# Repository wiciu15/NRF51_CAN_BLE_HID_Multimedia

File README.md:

#### *TLDR: Controlling spotify on the phone, with car's CAN bus*

This project is a ***work in progress***. Comes with no warranty. Vehicles CAN-bus is a powerful tool, ***use at your own risk***, author does not have responsibility for any damage on property or health.

Intended for ***2011-2013 Chevrolet Volt***, may work with other General Motors Global Platform A cars.
Uses own ***MCP2515 CAN controller*** chip library to interact with CAN-bus (Low-speed SWCAN/GMLAN in General Motors Vehicles).

Nordic ***NRF51822 microcontroler*** is in charge of Bluetooth LE connection and HID protocol.
HID report descriptor is custom and supports only 7 consumer control(multimedia) keys, like Play/Pause, Scan Next, Scan Prev, Mute.

CAN frames processing is offloaded to MCP2515 with usage of filters, to reduce uC usage and energy efficiency.
While MCP2515 is used in normal operating mode, device should not transmit anything other than error/ack frames.

PCB design needs some fixes and further testing. As of this moment 16Mhz crystal footprint is mirrored, MCP2515 INT pin needs a pullup resistor and SWDIO/RST pullup+optional power-on-reset 2.2u capacitor.

**[Project log on hackaday.io](https://hackaday.io/project/176834-chevy-volt-sw-can-ble-multimedia-control)**

Provided files are Eclipse GNU MCU Embedded project. To build it you need to also provide NRF SDK v12.3 (include directories), GCC arm-none-eabi compiler, and OpenOCD to use flash script (flash.bat file) with ST-Link v2 SWD programmer.

Software contains code from linux kernel CAN driver, and open-usb-can project by Fabio Baltieri.

**Software licensed under GNU General Public License v3.**
This program is free software: you can redistribute it and/or modify
it under the terms of the GNU General Public License as published by
the Free Software Foundation, either version 3 of the License, or
(at your option) any later version.

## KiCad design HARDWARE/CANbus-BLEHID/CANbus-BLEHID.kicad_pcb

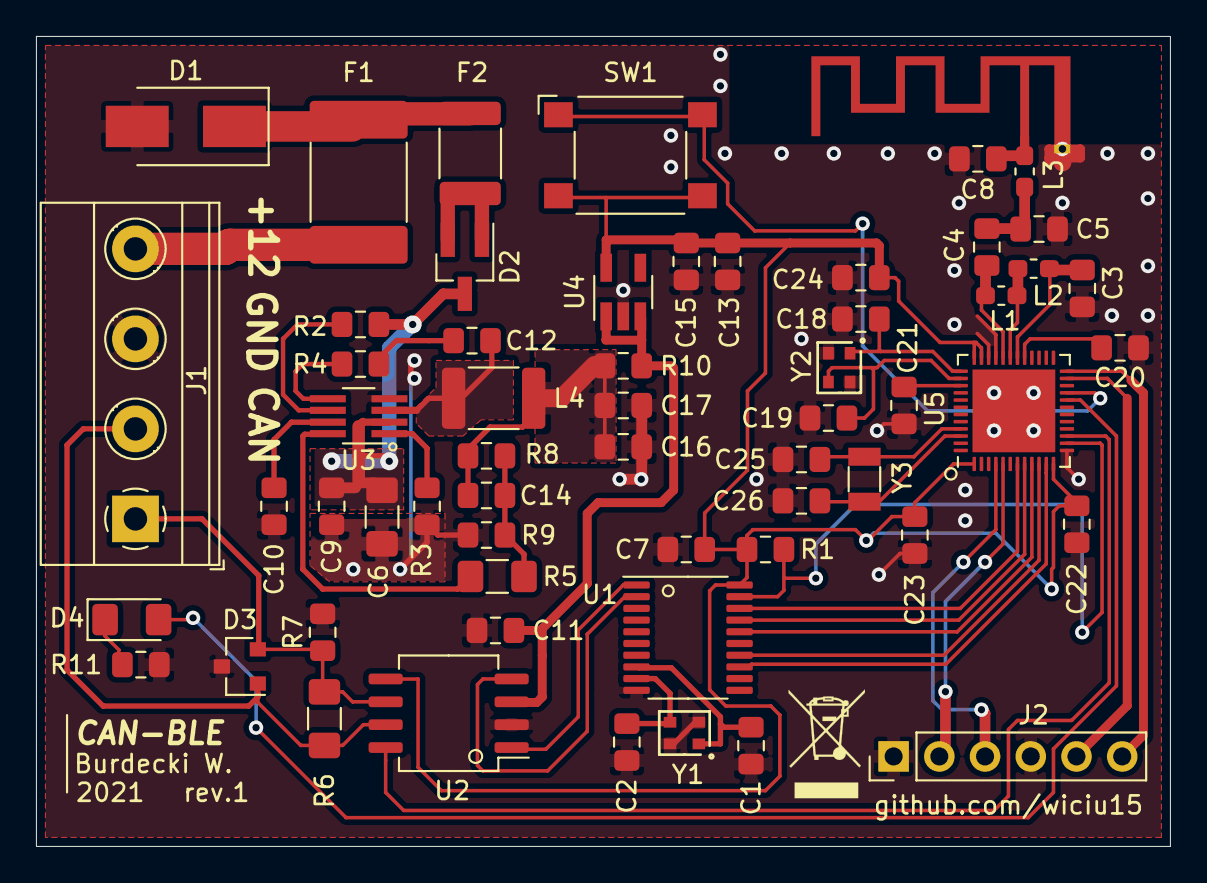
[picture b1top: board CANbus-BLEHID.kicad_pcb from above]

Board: 2 copper layers, 63.0 x 45.0 mm, 59 parts (0 on the bottom side), 47 nets.

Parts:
AE1: 2.45 GHz PCB antenna; Texas_SWRA117D_2.4GHz_Left
C1, C2, C14, C18, C19, C25, C26: 12pF; C_0805_2012Metric_Pad1.15x1.40mm_HandSolder
C3: 2.2n; C_0805_2012Metric_Pad1.15x1.40mm_HandSolder
C4: 3.9p; C_0805_2012Metric_Pad1.15x1.40mm_HandSolder
C5: 1p; C_0805_2012Metric_Pad1.15x1.40mm_HandSolder
C6: 10u 16V; C_1206_3216Metric_Pad1.42x1.75mm_HandSolder
C7, C9, C10, C11, C12, C15, C17, C20, C21, C22, C23: 100n; C_0805_2012Metric_Pad1.15x1.40mm_HandSolder
C8: 1.5p; C_0805_2012Metric_Pad1.15x1.40mm_HandSolder
C13, C16: 22u 6,3V; C_0805_2012Metric_Pad1.15x1.40mm_HandSolder
C24: 1n; C_0805_2012Metric_Pad1.15x1.40mm_HandSolder
D1: SM6T15CA; D_SMB_Handsoldering
D2: BAV70; SOT-23_Handsoldering
D3: PESD1CAN; SOT-23
D4: LED; LED_1206_3216Metric_Pad1.42x1.75mm_HandSolder
F1: 0ZCF0200AF2C; Fuse_2920_7451Metric_Pad2.10x5.45mm_HandSolder
F2: 0ZCK0010FF2G; Fuse_1812_4532Metric_Pad1.30x3.40mm_HandSolder
J1: AC300V-04P-5.0; TerminalBlock_Phoenix_MKDS-1,5-4_1x04_P5.00mm_Horizontal
J2: UART; PinHeader_1x06_P2.54mm_Vertical
L1: 4.7n; L_0603_1608Metric_Pad1.05x0.95mm_HandSolder
L2: 27n; L_0603_1608Metric_Pad1.05x0.95mm_HandSolder
L3: 3.3n; L_0603_1608Metric_Pad1.05x0.95mm_HandSolder
L4: NL12KTC5R6; L_1812_4532Metric_Pad1.30x3.40mm_HandSolder
R1: 10k; R_0805_2012Metric_Pad1.15x1.40mm_HandSolder
R2, R3: 75k; R_0805_2012Metric_Pad1.15x1.40mm_HandSolder
R4: 20R; R_0805_2012Metric_Pad1.15x1.40mm_HandSolder
R5: 20k; R_1206_3216Metric_Pad1.42x1.75mm_HandSolder
R6: 120R; R_1206_3216Metric_Pad1.42x1.75mm_HandSolder
R7, R10: 0R; R_0805_2012Metric_Pad1.15x1.40mm_HandSolder
R8: 40,2k; R_0805_2012Metric_Pad1.15x1.40mm_HandSolder
R9: 7,5k; R_0805_2012Metric_Pad1.15x1.40mm_HandSolder
R11: 1k; R_0805_2012Metric_Pad1.15x1.40mm_HandSolder
SW1: SW_Push_Dual; SW_SPST_Omron_B3FS-100xP
U1: MCP2515-xST; TSSOP-20_4.4x6.5mm_P0.65mm
U2: TLE7250V; SO-8_5.3x6.2mm_P1.27mm
U3: MP2315GJ-Z; TSOT-23-8_HandSoldering
U4: MIC5504-3.3YM5; SOT-23-5_HandSoldering
U5: nRF51822-QFAC; QFN-48-1EP_6x6mm_P0.4mm_EP4.6x4.6mm
Y1, Y2: 16M; XT224-16
Y3: 32,768k; Crystal_SMD_3215-2Pin_3.2x1.5mm

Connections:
+3V3: C7.2, C13.1, C15.2, C22.2, C23.2, C24.2, R1.1, SW1.3, SW1.4, U1.20, U2.5, U4.5, U5.1, U5.12, U5.35, U5.36
+5V: C11.2, R10.1, U2.3, U4.1, U4.3
ANT1: L1.2, L2.1, U5.31
ANT2: C4.2, L1.1, U5.32
CANH: D3.1, J1.2, R6.1, U2.7
CANL: D3.2, J1.1, R6.2, R7.1, U2.6
GND: AE1.2, C1.2, C2.2, C3.1, C5.1, C6.2, C7.1, C8.1, C9.1, C10.1, C11.1, C13.2, C15.1, C16.2, C17.1, C18.2, C19.2, C20.1, C21.1, C22.1, C23.1, C24.1, C25.1, C26.1, D1.2, D3.3, J1.3, J2.1, J2.4, R3.2, R7.2, R9.2, R11.1, U1.10, U2.2, U3.4, U4.2, U5.13, U5.33, U5.34, U5.49
MCP2515_INT: U1.13, U5.11
MCP2515_RST: R1.2, U1.19, U5.14
unnamed: AE1.1, C8.2, L3.2
unnamed: C1.1, U1.8, Y1.1
unnamed: C2.1, U1.9, Y1.2
unnamed: C4.1, C5.2, L3.1
unnamed: C6.1, C9.2, D2.3, R2.1, U3.2
unnamed: C10.2, U3.7
unnamed: C12.1, R4.1
unnamed: C12.2, L4.1, U3.3
unnamed: C14.1, R5.2, R8.2, R9.1
unnamed: C14.2, C16.1, C17.2, L4.2, R8.1, R10.2
unnamed: C18.1, U5.37, Y2.1
unnamed: C19.1, U5.38, Y2.2
unnamed: C20.2, U5.29
unnamed: C21.2, U5.39
unnamed: C25.2, U5.45, Y3.1
unnamed: C26.2, U5.46, Y3.2
unnamed: D1.1, F1.1, F2.2
unnamed: D2.1, D2.2, F2.1
unnamed: D4.1, R11.2
unnamed: D4.2, U5.20
unnamed: F1.2, J1.4
unnamed: R2.2, U3.6
unnamed: R3.1, U3.1
unnamed: R4.2, U3.5
unnamed: R5.1, U3.8
unnamed: SW1.1, SW1.2, U5.21
unnamed: U1.1, U2.1
unnamed: U1.2, U2.4
SPI_CS: U1.18, U5.7
SPI_MISO: U1.17, U5.8
SPI_MOSI: U1.16, U5.9
SPI_SCK: U1.14, U5.10
SWCLK: J2.6, U5.24
SWDIO: J2.5, U5.23
TLE7250_NEN: U2.8, U5.15
UART_RX: J2.2, U5.5
UART_TX: J2.3, U5.4
VDD_PA: C3.2, L2.2, U5.30

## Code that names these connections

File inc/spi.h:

/*
 * spi.h
 *
 *  Created on: 2 lut 2021
 *      Author: Wiktor
 */

#include "nrf_drv_spi.h"
#include "app_error.h"

#define SPI_INSTANCE 0

#define SPI_CS_PIN 3
#define SPI_MISO_PIN 4
#define SPI_MOSI_PIN 5
#define SPI_SCK_PIN 6

static const nrf_drv_spi_t spi=NRF_DRV_SPI_INSTANCE(SPI_INSTANCE);

ret_code_t spi0_init();
void spi0_cs_low();
void spi0_cs_high();
uint8_t spi0_transfer(uint8_t data);

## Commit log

2021-02-01 first working BLE HID
2021-04-04 Working CANbus library and interaction with BLE-HID
2021-04-04 Code cleanup and minor improvements
2021-04-04 Debug output
2021-04-11 PCB revision 1
2021-04-13 PCB production and assembly files
2021-05-02 power-saving, auto playing after connect, mcp2515 driver improvements
2021-05-22 PCB prototype code update
2021-07-04 changed mcp2515 clock speed
2021-07-10 erasing bonds with mute+PCB button and minor tweaks
2021-07-11 activity led fix
2021-07-11 LF clock changed from XTAL to internal RC and minor tweaks
2022-01-05 added steering wheel button inhibit
2022-04-08 increased steering wheel debouce delay
